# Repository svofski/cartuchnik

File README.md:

# cartuchnik
Flash Cartridge for Vectrex on LPC1769

Here's a youtube of an early test of Cartuchnik:
http://www.youtube.com/watch?v=1frCw8D-Ybc

And here's the loader menu:
http://www.youtube.com/watch?v=H1Qx4sDnVfg

This is a flash cartridge for Vectrex console. It uses internal flash memory LPC1769 for ROM storage. LPC1769 shows itself
to the host as a mass storage device where ROM files can be copied. There is a loader program that allows selection of
ROM file when Vectrex is first powered up. 64K roms are supported.

The hardware is LPC1769 Expresso board with an add-on board that plugs into the cartridge slot.

The project is very quirky, especially the mass storage part that's based on LPC port of LUFA, which was
extremely disappointingly buggy at the time of Cartuchnik development. However it works and can be used as a development
cartridge if you don't mind some messing around.

 * [kicad](kicad/) contains design files for LPC1769 Expresso board "shield" that plugs directly into the Vectrex.
 * [loader](loader/) is the loader code that's executed on the Vectrex and provides interface for ROM selection
 * [firmware](firmware/) LPC1769 code 

The loader should be compiled using [https://github.com/bcd/gcc]. I had trouble compiling the compiler on my system and here's a fork that builds on my machine: [https://github.com/svofski/gcc]

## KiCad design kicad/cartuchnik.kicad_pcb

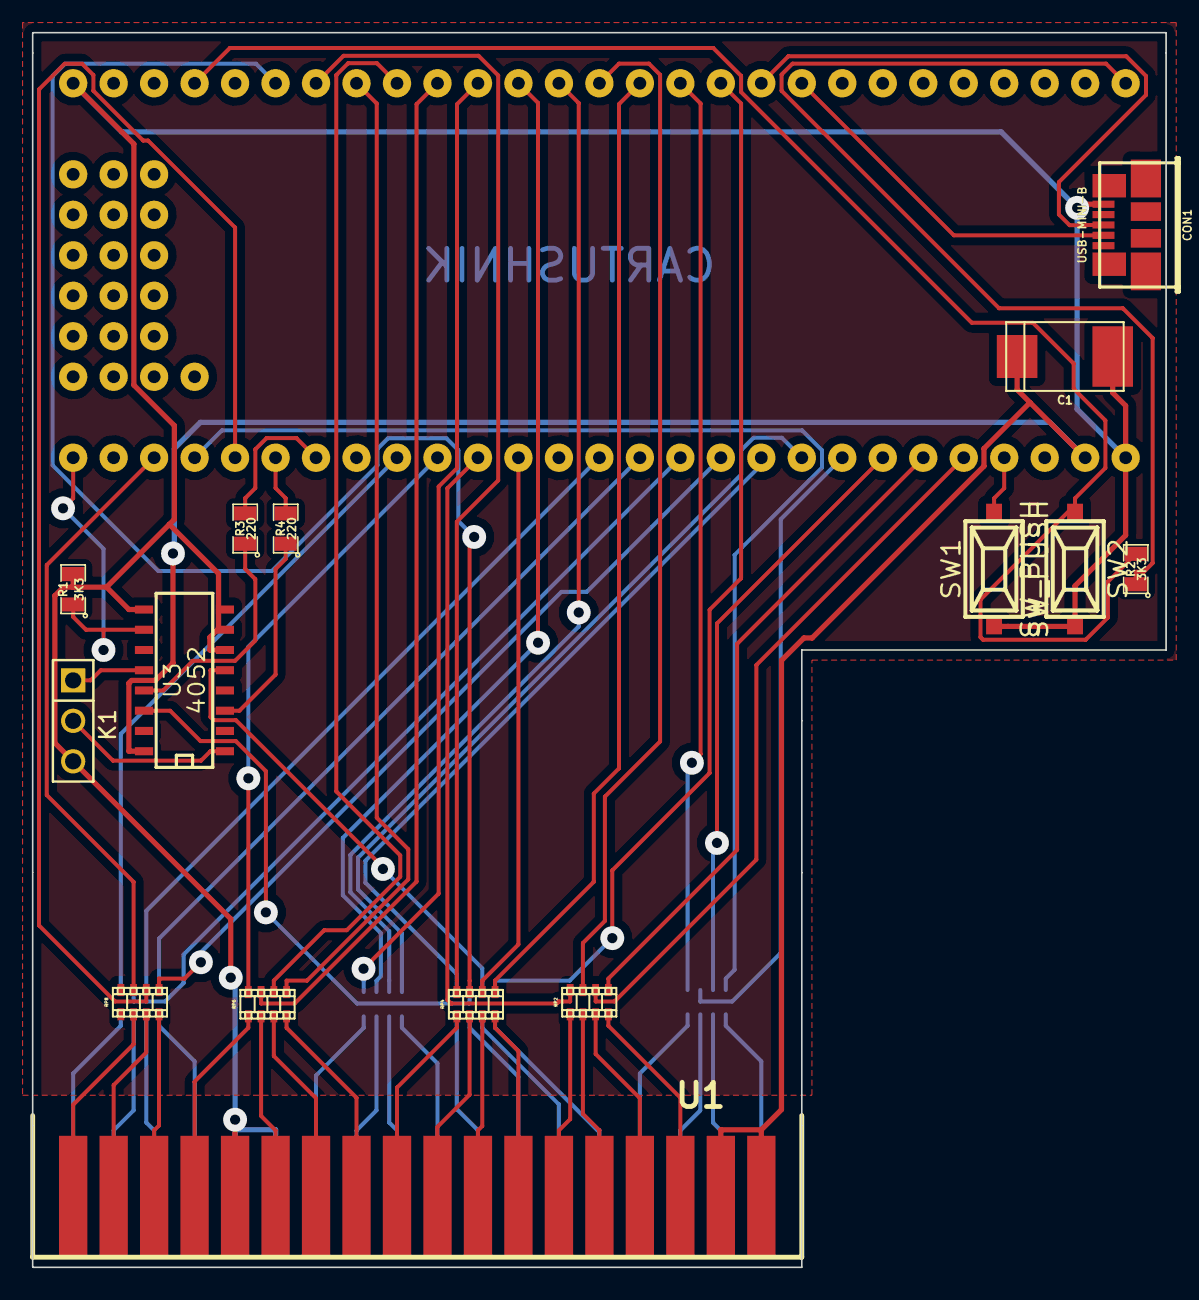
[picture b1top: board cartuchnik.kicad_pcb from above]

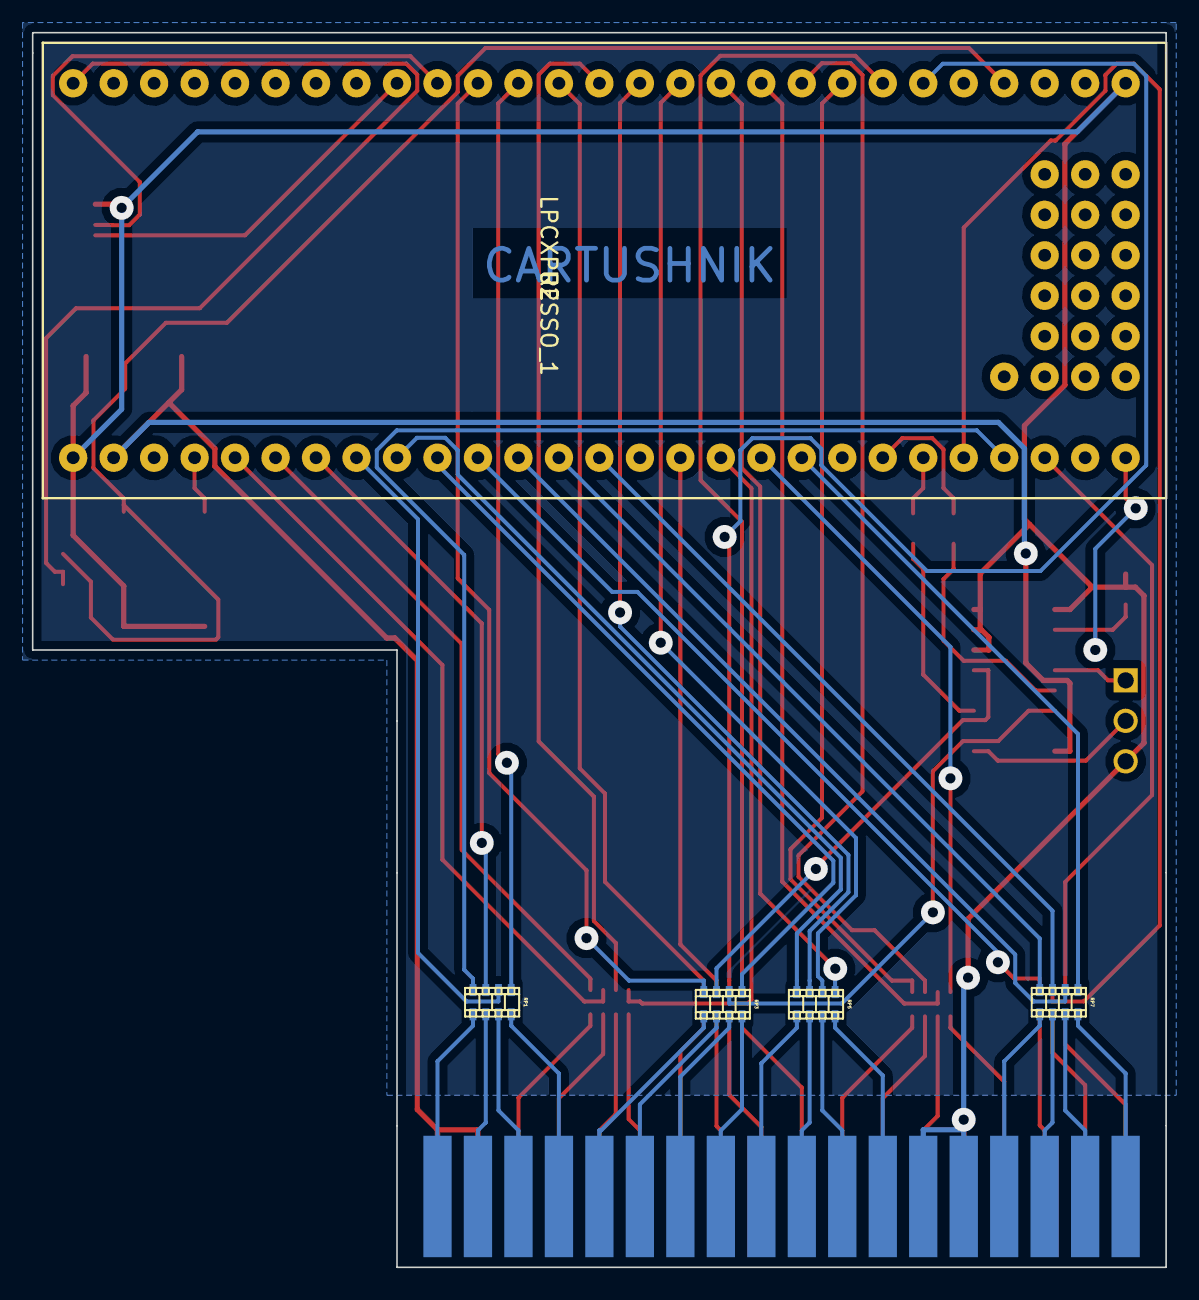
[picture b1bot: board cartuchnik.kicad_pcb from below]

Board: 2 copper layers, 71.1 x 77.5 mm, 20 parts (5 on the bottom side), 76 nets.

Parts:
C1: CP1; c_tant_D
CON1: USB-MINI-B; conn_usb_B_micro_smd
K1: CONN_3; PIN_ARRAY_3X1
R1, R2: 3K3; SM0805
R3, R4: 220; SM0805
RP1, RP2, RP3, RP4, RP5, RP6, RP7, RP8: R_PACK4; r_cat16-4
SW1, SW2: SW_PUSH; smd_push
U1: VECTREXCONN; VECTREX_CARTRIDGE
U2: LPCXPRESSO_1; LPCXPRESSO
U3: 4052; SO16E

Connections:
+3.3V: R2.1, U2.28
+5V: C1.1, U1.2, U1.4, U2.2, U3.16
/A0: RP5.8, U2.9
/A0x: RP5.1, U1.17
/A1: RP3.5, U2.10
/A1x: RP3.4, U1.15
/A2: RP3.6, U3.14
/A2/BOOT_TXD: R3.2, U2.21
/A2A3ENA: R1.1, U2.27, U3.10
/A2x: RP3.3, U1.13
/A3: RP3.7, U3.5
/A3/BOOT_RXD: R4.2, U2.22
/A3x: RP3.2, U1.11
/A4: RP3.8, U2.38
/A4x: RP3.1, U1.9
/A5: RP1.5, U2.39
/A5x: RP1.4, U1.7
/A6: RP1.6, U2.8
/A6x: RP1.3, U1.5
/A7: RP1.7, U2.7
/A7x: RP1.2, U1.3
/A8: RP2.1, U2.6
/A8x: RP2.8, U1.6
/A9: RP2.2, U2.5
/A9x: RP2.7, U1.8
/A10: RP4.1, U2.40
/A10x: RP4.8, U1.14
/A11: RP2.3, U2.41
/A11x: RP2.6, U1.10
/A12: RP7.8, U2.13
/A12x: RP7.1, U1.29
/A13: RP7.7, U2.14
/A13x: RP7.2, U1.31
/A14: RP7.6, U2.12
/A14x: RP7.3, U1.33
/B.6: RP7.5, U2.19
/B.6x: RP7.4, U1.35
/BOOT_RXD: K1.2, U3.1
/BOOT_TXD: K1.1, U3.12
/D0: RP5.7, U2.42
/D0x: RP5.2, U1.19
/D1: RP5.6, U2.43
/D1x: RP5.3, U1.21
/D2: RP5.5, U2.44
/D2x: RP5.4, U1.23
/D3: RP6.3, U2.45
/D3x: RP6.6, U1.26
/D4: RP6.2, U2.46
/D4x: RP6.7, U1.24
/D5: RP6.1, U2.47
/D5x: RP6.8, U1.22
/D6: RP4.4, U2.48
/D6x: RP4.5, U1.20
/D7: RP4.3, U2.49
/D7x: RP4.6, U1.18
/R/~W: RP6.4, U2.18
/R/~Wx: RP6.5, U1.30
/USBD+: CON1.3, U2.37
/USBD-: CON1.2, U2.36
/~CART: RP8.1, U2.11
/~CARTx: RP8.8, U1.32
/~CE: RP4.2, U2.16
/~CEx: RP4.7, U1.16
/~HALT: RP1.8, U2.24
/~HALTx: RP1.1, U1.1
/~IRQ: RP8.3, U2.25
/~IRQx: RP8.6, U1.36
/~NMI: RP8.2, U2.23
/~NMIx: RP8.7, U1.34
/~OE: RP2.4, U2.17
/~OEx: RP2.5, U1.12
/~RESET: SW1.2, U2.4
GND: C1.2, CON1.5, K1.3, R1.2, SW1.1, SW2.2, U1.25, U1.27, U1.28, U2.1, U2.54, U3.6, U3.7, U3.8, U3.9
unnamed: R3.1, U3.13
unnamed: R2.2, SW2.1, U2.51
unnamed: R4.1, U3.3

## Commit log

2014-09-01 new repo from the old one at https://code.google.com/p/svofski/
2014-09-02 .swp
2014-09-02 trying vim modeling
2014-09-02 mode line proven ineffective, github guesses gas mode right but has shitty assembly highlighter
2014-09-02 implemented ROM selection: rom index is a write to address $0000 the code that does this is copied into RAM to avoid the nasty
2014-09-05 launcher routine cleanup
2014-09-09 display rom name in the after selection animation
